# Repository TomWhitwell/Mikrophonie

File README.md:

# Mikrophonie

Design files for the Music Thing Modular Mikrophonie Module.  

Full details available at http://www.musicthing.co.uk

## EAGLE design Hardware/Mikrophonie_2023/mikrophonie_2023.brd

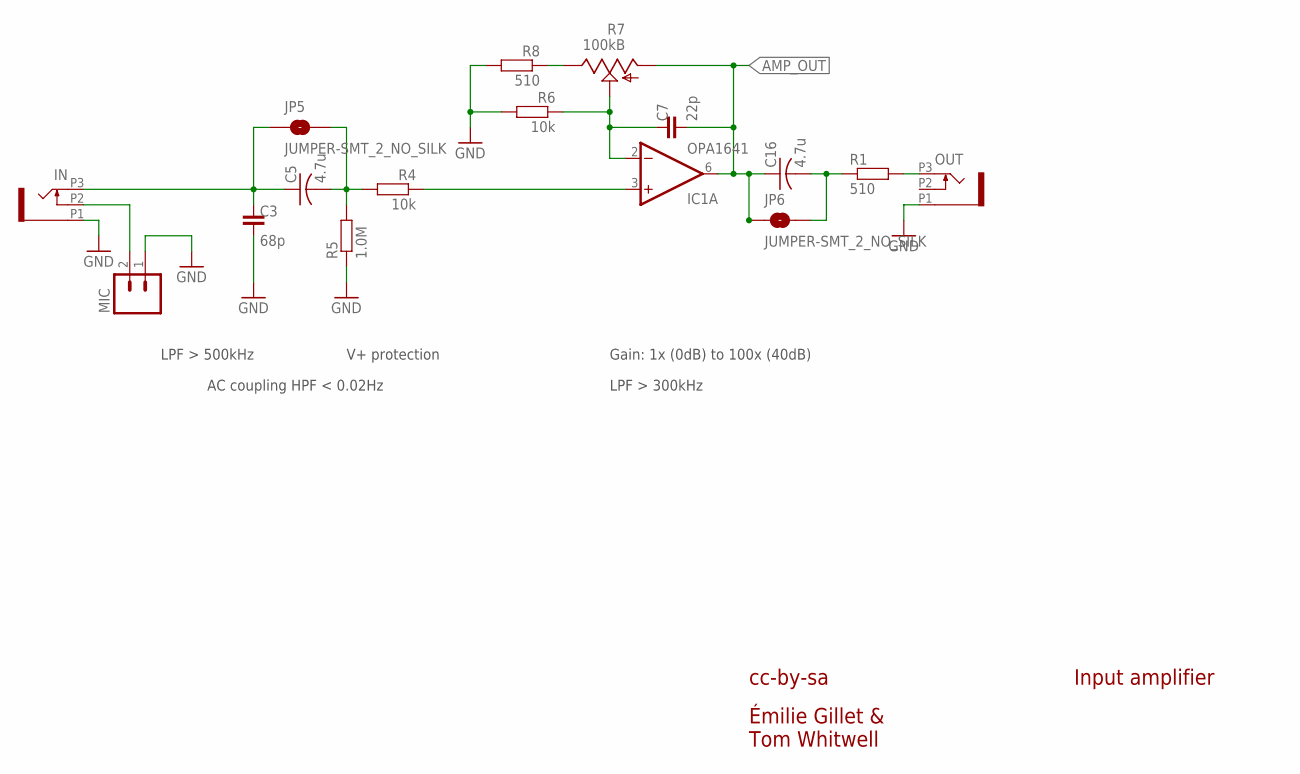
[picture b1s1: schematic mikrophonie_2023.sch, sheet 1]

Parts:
C3: 68p; C0402-90
C5, C16: 4.7u; C0603
C7: 22p; C0402-90
IC1: OPA1641; MSOP8
IN: PJ301_THONKICONN6; WQP_PJ_301M6
JP5, JP6: JUMPER-SMT_2_NO_SILK; SMT-JUMPER_2_NO_SILK
MIC: M02TINY; 1X02_TINY
OUT: PJ301_THONKICONN6; WQP_PJ_301M6
R1, R8: 510; C0402-90
R4, R6: 10k; C0402-90
R5: 1.0M; C0402-90
R7: 100kB; ALPS_POT_VERTICAL_PS

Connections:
AMP_OUT: C7.2, C16.1, IC1.6 (OUT), JP6.1, R7.P$3 (A); also elsewhere on the board
GND: C3.2, IN.P1 (1), MIC.1, OUT.P1 (1), R5.1, R6.2, R8.2; also elsewhere on the board
unnamed: IC1.3 (+IN), R4.1
unnamed: OUT.P3 (3), R1.2
unnamed: C3.1, C5.1, IN.P3 (3), JP5.1
unnamed: IN.P2 (2), MIC.2
unnamed: C7.1, IC1.2 (-IN), R6.1, R7.P$2 (S)
unnamed: C5.2, JP5.2, R4.2, R5.2
unnamed: R7.P$1 (E), R8.1
unnamed: C16.2, JP6.2, R1.1

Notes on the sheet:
cc-by-sa
Input amplifier
Gain: 1x (0dB) to 100x (40dB)
LPF > 500kHz
V+ protection
LPF > 300kHz
AC coupling HPF < 0.02Hz
Émilie Gillet & Tom Whitwell

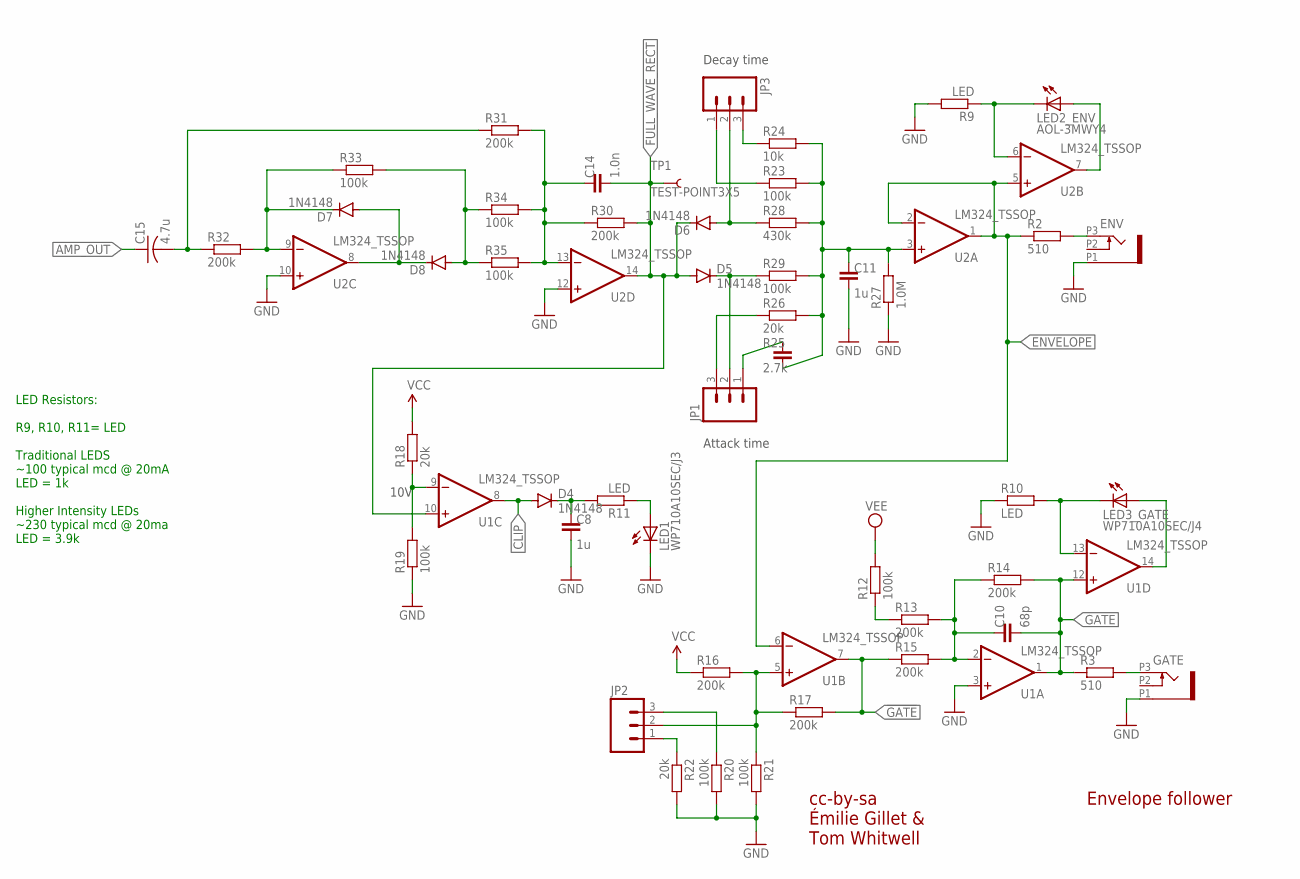
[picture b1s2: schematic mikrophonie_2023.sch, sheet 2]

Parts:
C8, C11: 1u; C0402-90
C10: 68p; C0402-90
C14: 1.0n; C0402-90
C15: 4.7u; C0603
D4, D5, D6, D7, D8: 1N4148; SOD523
ENV: PJ301_THONKICONN6; WQP_PJ_301M6
GATE: PJ301_THONKICONN6; WQP_PJ_301M6
JP1, JP2, JP3: M03PTH; 1X03
LED1: WP710A10SEC/J3; LED3MM
LED2_ENV: AOL-3MWY4; LED3MM
LED3_GATE: WP710A10SEC/J4; LED3MM
R2, R3: 510; C0402-90
R9, R10, R11: LED; C0402-90
R12, R19, R20, R21, R23, R29, R33, R34, R35: 100k; C0402-90
R13, R14, R15, R16, R17, R30, R31, R32: 200k; C0402-90
R18, R22, R26: 20k; C0402-90
R24: 10k; C0402-90
R25: 2.7k; C0402-90
R27: 1.0M; C0402-90
R28: 430k; C0402-90
TP1: TEST-POINT3X5; PAD.03X.05
U1, U2: LM324_TSSOP; SOP65P640X120-14N

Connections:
!GATE: R15.1, R17.2, U1.7 (OUT)
AMP_OUT: C15.1; also elsewhere on the board
AMP_OUT_AC: C15.2, R31.1, R32.1
CLIP: D4.A, U1.8 (OUT)
ENVELOPE: R2.1, U1.6 (-IN), U2.1 (OUT), U2.2 (-IN), U2.5 (+IN)
FULL_WAVE_RECT: C14.2, D5.A, D6.C, R30.2, TP1.P$1, U1.10 (+IN), U2.14 (OUT)
GATE: C10.2, R3.1, R14.2, U1.1 (OUT), U1.12 (+IN)
GND: C8.2, C11.2, ENV.P1 (1), GATE.P1 (1), LED1.K (C), R9.2, R10.1, R19.1, R20.2, R21.2, R22.2, R27.1, U1.3 (+IN), U2.10 (+IN), U2.12 (+IN); also elsewhere on the board
unnamed: D7.A, D8.C, U2.8 (OUT)
unnamed: C10.1, R13.2, R14.1, R15.2, U1.2 (-IN)
unnamed: D7.C, R32.2, R33.1, U2.9 (-IN)
unnamed: D8.A, R33.2, R34.1, R35.1
unnamed: C14.1, R30.1, R31.2, R34.2, R35.2, U2.13 (-IN)
unnamed: ENV.P3 (3), R2.2
unnamed: LED2_ENV.K (C), R9.1, U2.6 (-IN)
unnamed: D5.C, JP1.2, R29.1
unnamed: C11.1, R23.2, R24.2, R25.2, R26.2, R27.2, R28.2, R29.2, U2.3 (+IN)
unnamed: JP3.3, R24.1
unnamed: JP3.1, R23.1
unnamed: D6.A, JP3.2, R28.1
unnamed: JP1.1, R25.1
unnamed: JP1.3, R26.1
unnamed: R18.1, R19.2, U1.9 (-IN)
unnamed: C8.1, D4.C, R11.2
unnamed: LED2_ENV.A, U2.7 (OUT)
unnamed: LED1.A, R11.1
unnamed: GATE.P3 (3), R3.2
unnamed: JP2.2, R16.2, R17.1, R21.1, U1.5 (+IN)
unnamed: JP2.1, R22.1
unnamed: JP2.3, R20.1
unnamed: LED3_GATE.K (C), R10.2, U1.13 (-IN)
unnamed: LED3_GATE.A, U1.14 (OUT)
unnamed: R12.1, R13.1
VCC: R16.1, R18.2; also elsewhere on the board
VEE: R12.2; also elsewhere on the board

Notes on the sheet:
cc-by-sa
Envelope follower
Decay time
Attack time
10V
Émilie Gillet & Tom Whitwell
LED Resistors: R9, R10, R11= LED Traditional LEDS ~100 typical mcd @ 20mA LED = 1k Higher Intensity LEDs ~230 typical mcd @ 20ma LED = 3.9k

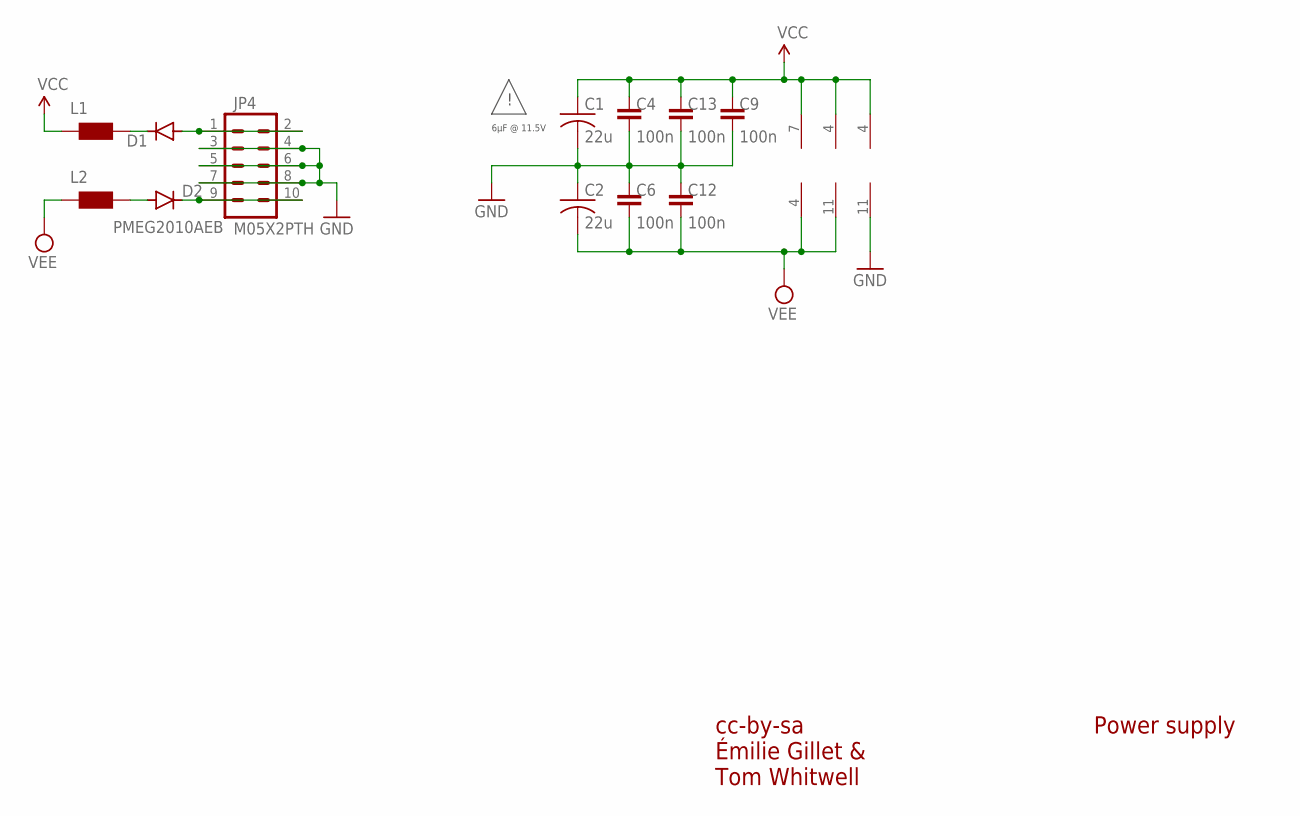
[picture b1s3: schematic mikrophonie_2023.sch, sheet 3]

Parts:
C1, C2: 22u; C1206
C4, C6, C9, C12, C13: 100n; C0402-90
D1, D2: PMEG2010AEB; SOD523
IC1: OPA1641; MSOP8
JP4: M05X2PTH; AVR_ICSP
L1, L2: WE-CBF_0603; 0603
U1, U2: LM324_TSSOP; SOP65P640X120-14N

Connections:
GND: C1.2, C2.1, C4.2, C6.1, C9.2, C12.1, C13.2, JP4.3, JP4.4, JP4.5, JP4.6, JP4.7, JP4.8, U1.11 (V-); also elsewhere on the board
unnamed: D1.A, JP4.1, JP4.2
unnamed: D2.C, JP4.9, JP4.10
unnamed: D1.C, L1.2
unnamed: D2.A, L2.2
VCC: C1.1, C4.1, C9.1, C13.1, IC1.7 (V+), L1.1, U1.4 (V+), U2.4 (V+); also elsewhere on the board
VEE: C2.2, C6.2, C12.2, IC1.4 (V-), L2.1, U2.11 (V-); also elsewhere on the board

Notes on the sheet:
cc-by-sa
Power supply
6µF @ 11.5V
Émilie Gillet & Tom Whitwell

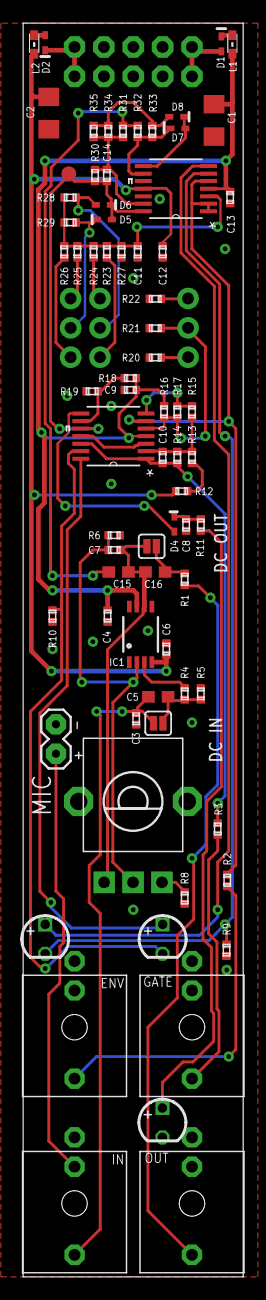
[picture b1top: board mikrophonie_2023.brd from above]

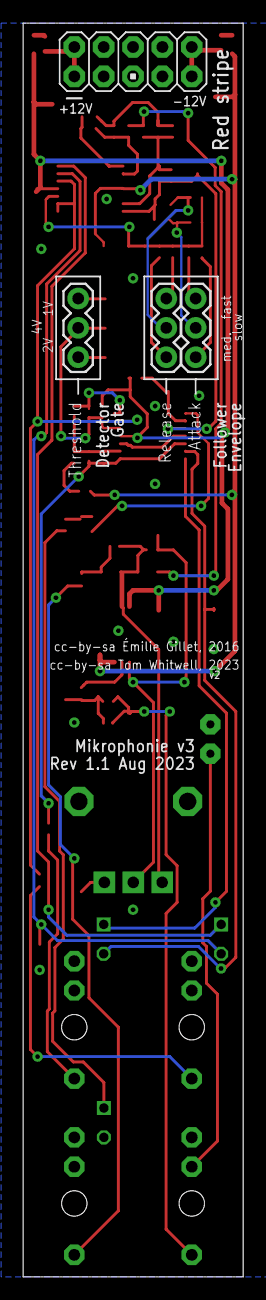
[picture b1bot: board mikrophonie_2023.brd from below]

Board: 2 copper layers, 19.0 x 108.4 mm, 78 parts (4 on the bottom side), 47 nets.

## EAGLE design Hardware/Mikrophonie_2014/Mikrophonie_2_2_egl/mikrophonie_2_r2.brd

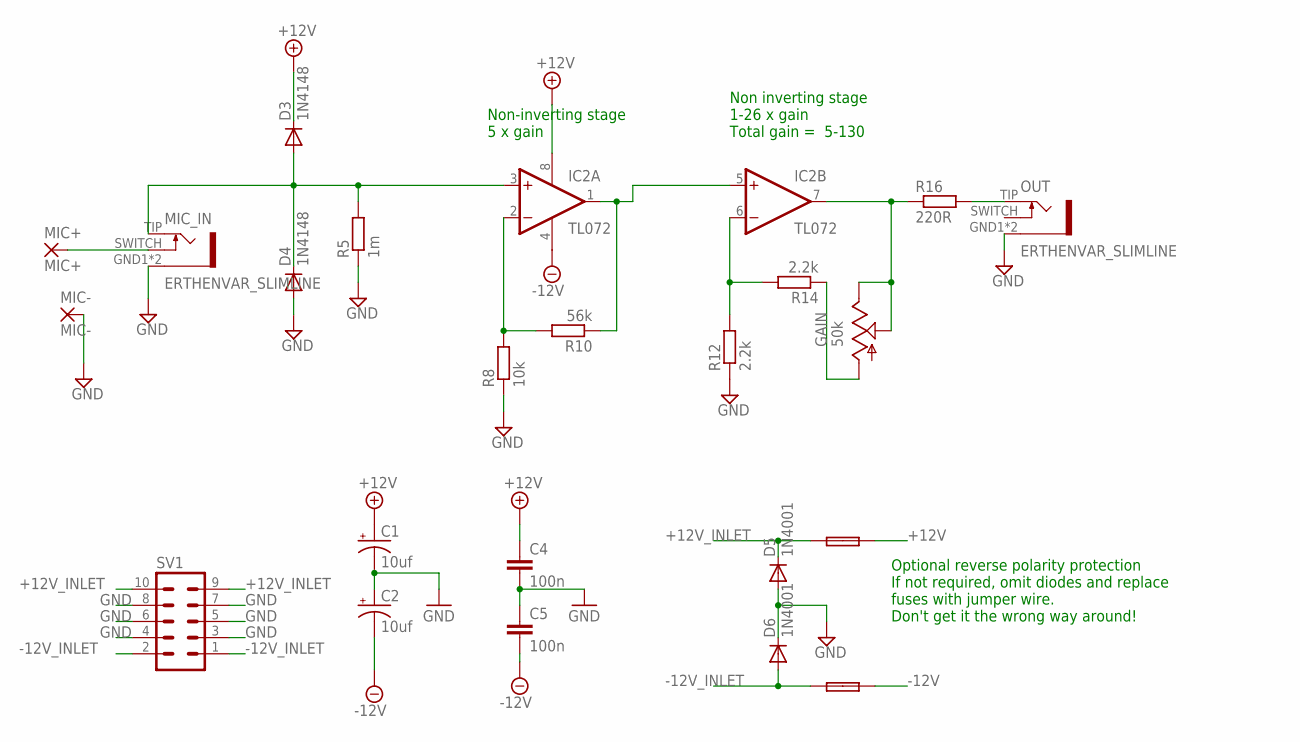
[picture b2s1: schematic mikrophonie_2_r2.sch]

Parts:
1: FUSE; C050H075X075
C1, C2: 10uf; CPOL-RADIAL-10UF-25V
C4, C5: 100n; C050-024X044
D3, D4: 1N4148; DO35-7
D5, D6: 1N4001; DO41-10
FUSE: FUSE; C050H075X075
GAIN: 50k; EVUF
IC2: TL072; DIL08
MIC+: MIC+; LONG_PAD_1
MIC-: MIC-; LONG_PAD_1
MIC_IN: ERTHENVAR_SLIMLINE
OUT: ERTHENVAR_SLIMLINE
R5: 1m; 0207/10
R8: 10k; 0207/10
R10: 56k; 0207/10
R12, R14: 2.2k; 0207/10
R16: 220R; 0207/10
SV1: 10_PIN_HEADER; MA05-2

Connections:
+12V: 1.2, C1.1 (+), C4.1, D3.C, IC2.8 (V+)
+12V_INLET: 1.1, D5.C, SV1.9, SV1.10
-12V: C2.2 (-), C5.2, FUSE.2, IC2.4 (V-)
-12V_INLET: D6.A, FUSE.1, SV1.1, SV1.2
GND: C1.2 (-), C2.1 (+), C4.2, C5.1, D4.A, D5.A, D6.C, MIC-.P$1, MIC_IN.GND1 (5), MIC_IN.GND2 (5), OUT.GND1 (5), OUT.GND2 (5), R5.1, R8.1, R12.1, SV1.3, SV1.4, SV1.5, SV1.6, SV1.7, SV1.8
unnamed: MIC+.P$1, MIC_IN.SWITCH (4)
unnamed: D3.A, D4.C, IC2.3 (+IN), MIC_IN.TIP (3), R5.2
unnamed: IC2.2 (-IN), R8.2, R10.2
unnamed: IC2.1 (OUT), IC2.5 (+IN), R10.1
unnamed: GAIN.1 (A), R14.1
unnamed: IC2.6 (-IN), R12.2, R14.2
unnamed: GAIN.2 (S), GAIN.3 (E), IC2.7 (OUT), R16.1
unnamed: OUT.TIP (3), R16.2

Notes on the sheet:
Non-inverting stage 5 x gain
Non inverting stage 1-26 x gain Total gain = 5-130
Optional reverse polarity protection If not required, omit diodes and replace fuses with jumper wire. Don't get it the wrong way around!

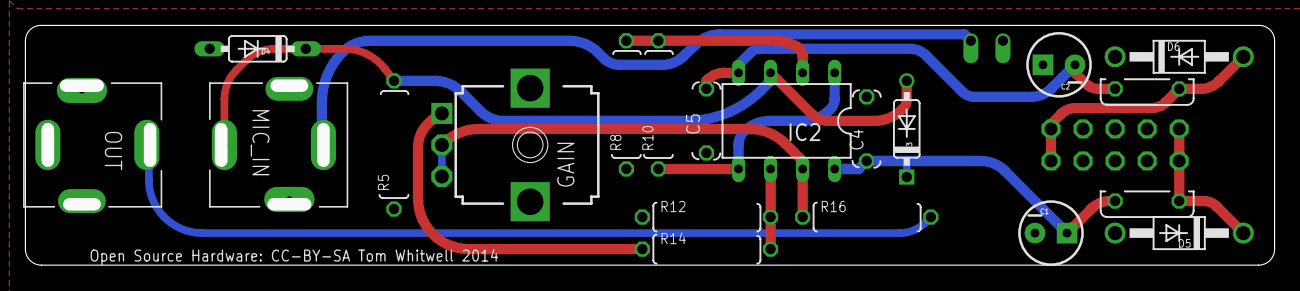
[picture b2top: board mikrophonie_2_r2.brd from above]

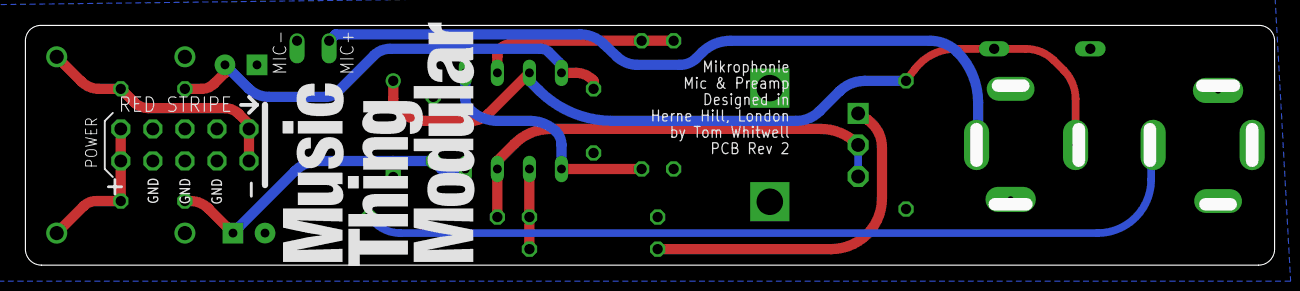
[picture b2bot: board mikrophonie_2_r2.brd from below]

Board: 4 copper layers, 98.0 x 18.0 mm, 24 parts (2 on the bottom side), 13 nets.

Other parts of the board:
U$2: MTM_2CM_SCREEN_200DPI

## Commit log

2018-01-01 Upload files
2023-10-18 Uploaded Mikrophonie 2023 Edition

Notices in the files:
Hardware/Mikrophonie_2014/Mikrophonie_2_2_egl/mikrophonie_2_r2.brd:
Open Source Hardware: CC-BY-SA Tom Whitwell 2014
Hardware/Mikrophonie_2023/mikrophonie_2023.brd:
cc-by-sa Émilie Gillet, 2016
cc-by-sa Tom Whitwell, 2023
parts and their libraries:
SparkFun-Passives: Licensing: CC v3.0 Share-Alike You are welcome to use this library for commercial purposes.
SparkFun-Jumpers: Licensing: Creative Commons ShareAlike 4.0 International - https://creativecommons.org/licenses/by-sa/4.0
